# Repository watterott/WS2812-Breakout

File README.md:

# WS2812-Breakout
Breakouts with WS2812 intelligent RGB-LED.

* WS2812 RGB-LED with built-in controller with serial interface
* 3 pin connection: VCC, GND, Data
* Controllable with Adafruit NeoPixel Library
* Note: for protection connect a >= 300 ohm resistor between the LED data input and controller output pin.
* Open-Source and released under the [Creative Commons Attribution Share-Alike License](https://creativecommons.org/licenses/by-sa/4.0/).
* **[Documentation on learn.watterott.com](https://learn.watterott.com)**

## Videos
*

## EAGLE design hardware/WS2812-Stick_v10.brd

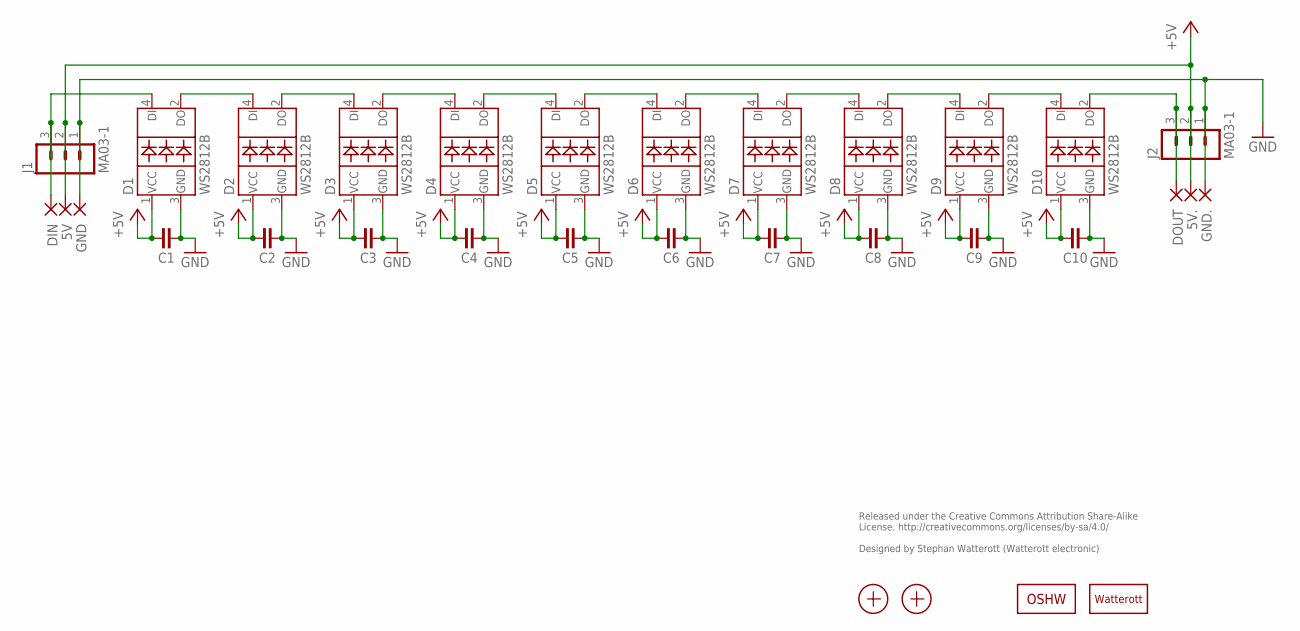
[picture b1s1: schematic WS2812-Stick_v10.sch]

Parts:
5V, 5V.: SMD2; SMD1,27-2,54
C1, C2, C3, C4, C5, C6, C7, C8, C9, C10: CAPACITOR-0402; C0402
D1, D2, D3, D4, D5, D6, D7, D8, D9, D10: WS2812B
DIN: SMD2; SMD1,27-2,54
DOUT: SMD2; SMD1,27-2,54
GND, GND.: SMD2; SMD1,27-2,54
J1, J2: MA03-1
LOGO1: OSHW_LOGOX0070; OSHW_6X70
LOGO2: LOGO-PLACE; LOGO_TPLACE
X1, X2: PASSER-07; PASSER_07MM

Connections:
+5V: 5V.1, 5V..1, C1.2, C2.2, C3.2, C4.2, C5.2, C6.2, C7.2, C8.2, C9.2, C10.2, D1.1 (VCC), D2.1 (VCC), D3.1 (VCC), D4.1 (VCC), D5.1 (VCC), D6.1 (VCC), D7.1 (VCC), D8.1 (VCC), D9.1 (VCC), D10.1 (VCC), J1.2, J2.2
GND: C1.1, C2.1, C3.1, C4.1, C5.1, C6.1, C7.1, C8.1, C9.1, C10.1, D1.3 (GND), D2.3 (GND), D3.3 (GND), D4.3 (GND), D5.3 (GND), D6.3 (GND), D7.3 (GND), D8.3 (GND), D9.3 (GND), D10.3 (GND), GND.1, GND..1, J1.1, J2.1
unnamed: D1.4 (DI), DIN.1, J1.3
unnamed: D1.2 (DO), D2.4 (DI)
unnamed: D2.2 (DO), D3.4 (DI)
unnamed: D3.2 (DO), D4.4 (DI)
unnamed: D4.2 (DO), D5.4 (DI)
unnamed: D5.2 (DO), D6.4 (DI)
unnamed: D6.2 (DO), D7.4 (DI)
unnamed: D7.2 (DO), D8.4 (DI)
unnamed: D8.2 (DO), D9.4 (DI)
unnamed: D9.2 (DO), D10.4 (DI)
unnamed: D10.2 (DO), DOUT.1, J2.3

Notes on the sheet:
Released under the Creative Commons Attribution Share-Alike License. http://creativecommons.org/licenses/by-sa/4.0/ Designed by Stephan Watterott (Watterott electronic)

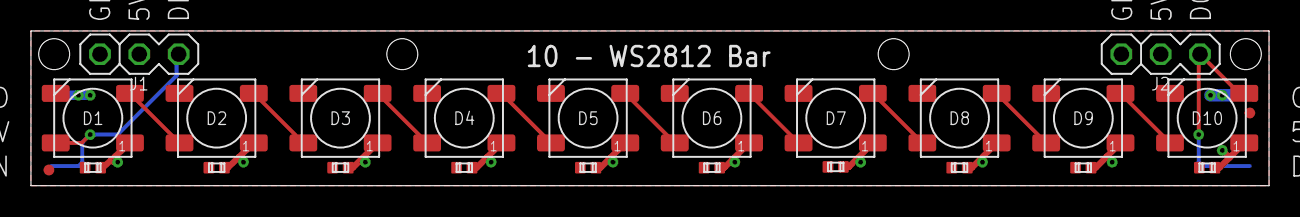
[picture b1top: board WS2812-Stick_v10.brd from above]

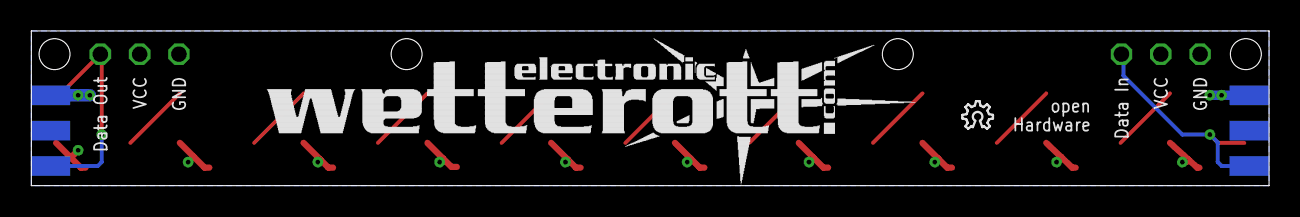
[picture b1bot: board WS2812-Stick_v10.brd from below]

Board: 2 copper layers, 80.0 x 10.0 mm, 32 parts (8 on the bottom side), 13 nets.

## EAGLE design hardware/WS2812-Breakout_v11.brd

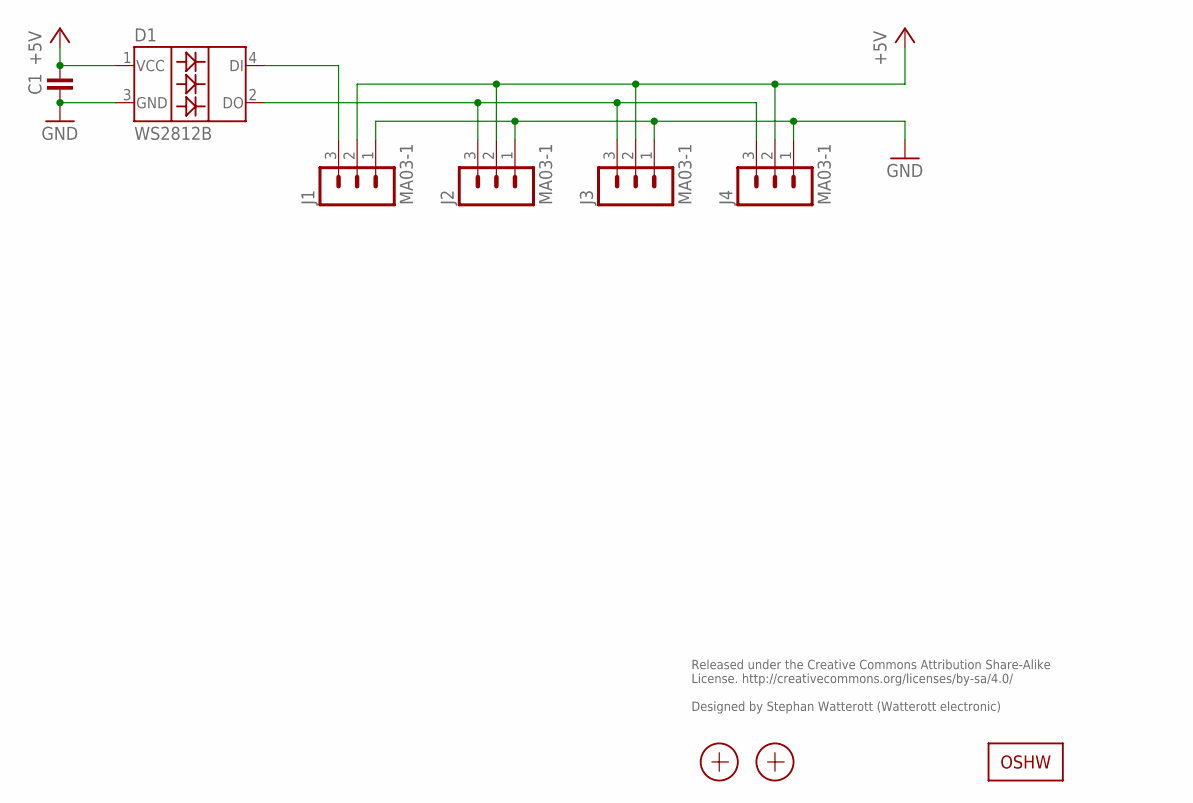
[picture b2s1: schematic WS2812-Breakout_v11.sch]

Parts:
C1: CAPACITOR-0402; C0402
D1: WS2812B
J1, J2, J3, J4: MA03-1
LOGO1: OSHW_LOGOX0070; OSHW_6X70
X1, X2: PASSER-07; PASSER_07MM

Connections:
+5V: C1.2, D1.1 (VCC), J1.2, J2.2, J3.2, J4.2
GND: C1.1, D1.3 (GND), J1.1, J2.1, J3.1, J4.1
unnamed: D1.4 (DI), J1.3
unnamed: D1.2 (DO), J2.3, J3.3, J4.3

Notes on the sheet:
Released under the Creative Commons Attribution Share-Alike License. http://creativecommons.org/licenses/by-sa/4.0/ Designed by Stephan Watterott (Watterott electronic)

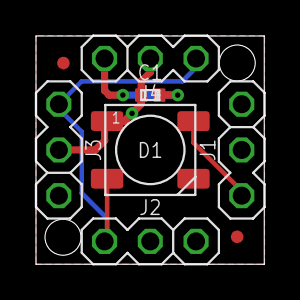
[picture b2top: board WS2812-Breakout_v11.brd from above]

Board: 2 copper layers, 12.7 x 12.7 mm, 9 parts (1 on the bottom side), 4 nets.
